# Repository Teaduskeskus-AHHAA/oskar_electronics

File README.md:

# Oskar III electronics

This repository contains the hardware and firmware sources required to build the electronic controllers for Science Centre AHHAA's Oskar III.

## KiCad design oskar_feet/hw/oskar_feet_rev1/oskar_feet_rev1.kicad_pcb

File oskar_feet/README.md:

# Oskar III electronics/Feet

This folder contains the contains the hardware and firmware sources required to build the electronic controller for Oskar III's feet. This controller handles the drivetrain and power control for the rest of the robot.

# Feature list

* IR Corner sensors
* Wheel engage-disengage control and detection
* Wheel drive
* Kneel drive
* BMS comms

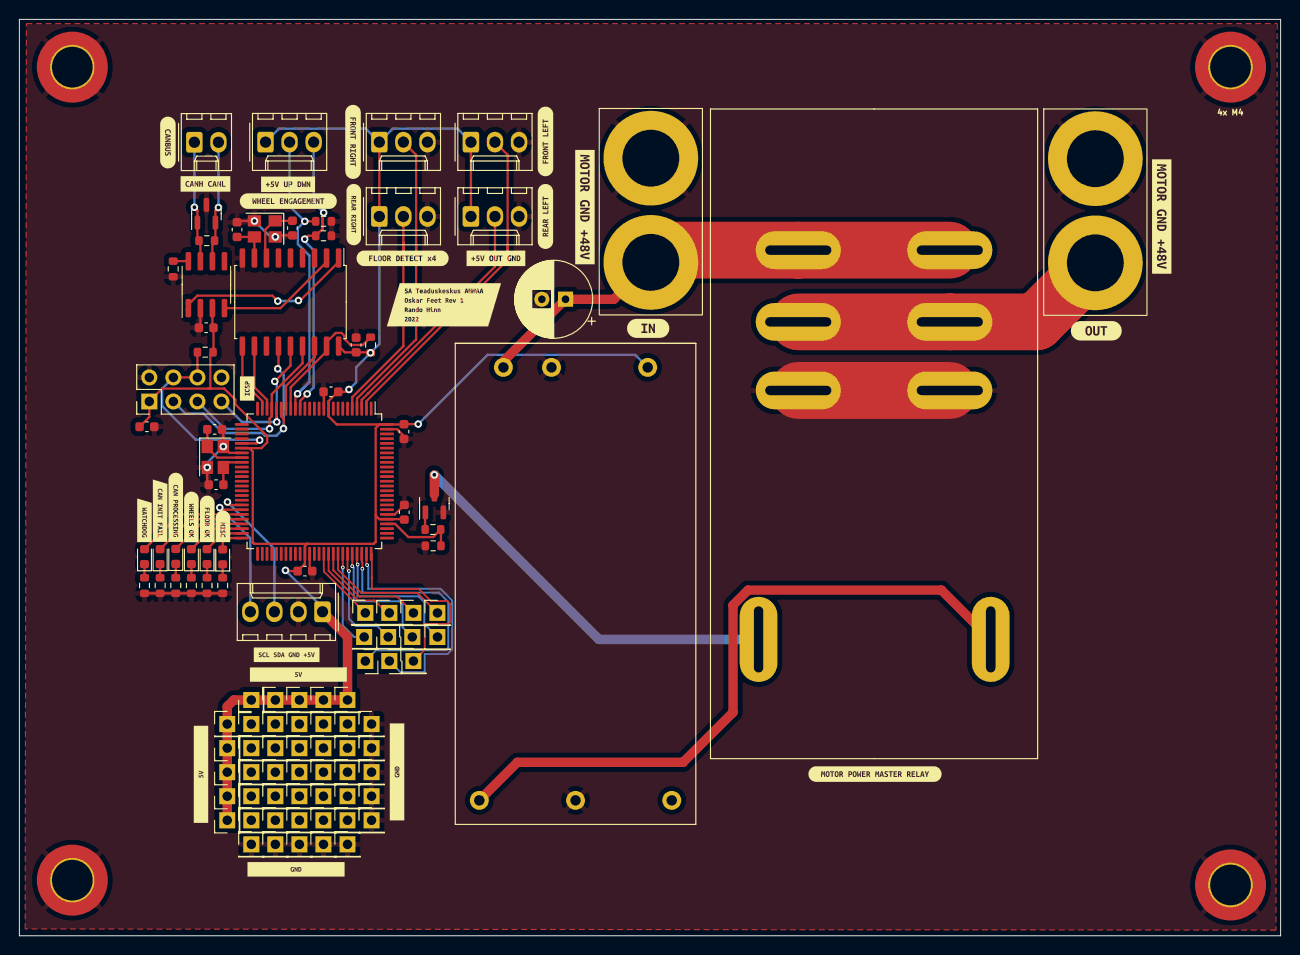
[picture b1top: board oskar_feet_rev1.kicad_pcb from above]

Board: 2 copper layers, 133.2 x 96.8 mm, 139 parts (0 on the bottom side), 56 nets.

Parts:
C1, C2, C5, C6, C7, C10, C11: 10u; C_0603_1608Metric
C3, C4, C8, C9: TBD; C_0603_1608Metric
C12: TBD; CP_Radial_D8.0mm_P2.50mm
D1: PESD2CAN; SOT-23
D2, D3, D4, D5, D6, D7: LED; LED_0603_1608Metric
H1, H2, H3, H4: MountingHole_Pad; MountingHole_4.3mm_M4_DIN965_Pad_TopBottom
J1: PROG; PinHeader_2x04_P2.54mm_Vertical
J2: Conn_01x02_Male; Molex_KK-254_AE-6410-02A_1x02_P2.54mm_Vertical
J3, J4, J5, J6, J9: Conn_01x03_Male; Molex_KK-254_AE-6410-03A_1x03_P2.54mm_Vertical
J7: Conn_01x02_Female; XT90
J8: Conn_01x02_Male; XT90
J10: Conn_01x04_Male; Molex_KK-254_AE-6410-04A_1x04_P2.54mm_Vertical
J11, J12, J13, J14, J15, J16, J17, J18, J19, J20, J21, J22, J23, J24, J25, J26, J27, J28, J29, J30, J31, J32, J33, J34, J35, J36, J37, J38, J39, J40, J41, J42, J43, J44, J45, J46, J47, J48, J49, J50, J51, J52, J53, J54, J55, J56, J58, J59, J60, J61, J62, J63, J64, J65, J66, J67: Conn_01x01_Male; PinHeader_1x01_P2.54mm_Vertical
K1: T92P11D22-12
Q1: BC817; SOT-23
R1, R2, R4, R6, R13, R14: 10k; R_0603_1608Metric
R3: 120; R_0603_1608Metric
R5: 330; R_0603_1608Metric
R7, R8, R9, R10, R11, R12: tbd; R_0603_1608Metric
U1: ATmega2560-16A; TQFP-100_14x14mm_P0.5mm
U2: MCP2515-xSO; SOIC-18W_7.5x11.6mm_P1.27mm
U3: MCP2551-I-SN; SOIC-8_3.9x4.9mm_P1.27mm
U4: MPRB4812LD-30W
Y1, Y3: Crystal_GND24; Crystal_SMD_Abracon_ABM8G-4Pin_3.2x2.5mm
kibuzzard-61FBB8B4: G***; kibuzzard-61FBB8B4
kibuzzard-61FBB827: G***; kibuzzard-61FBB827
kibuzzard-61FBB893: G***; kibuzzard-61FBB893
kibuzzard-61FBB948: G***; kibuzzard-61FBB948
kibuzzard-61FBBA02: G***; kibuzzard-61FBBA02
kibuzzard-61FBBA21: G***; kibuzzard-61FBBA21
kibuzzard-61FBBAE0: G***; kibuzzard-61FBBAE0
kibuzzard-61FC1DAC: G***; kibuzzard-61FC1DAC
kibuzzard-620D462F: G***; kibuzzard-620D462F
kibuzzard-620D4636: G***; kibuzzard-620D4636
kibuzzard-620D4649, kibuzzard-620D4649#2: G***; kibuzzard-620D4649
kibuzzard-620F6F5F: G***; kibuzzard-620F6F5F
kibuzzard-620F6F6C: G***; kibuzzard-620F6F6C
kibuzzard-622DE651: G***; kibuzzard-622DE651
kibuzzard-622E021D: G***; kibuzzard-622E021D
kibuzzard-622E0128: G***; kibuzzard-622E0128
kibuzzard-622E0245: G***; kibuzzard-622E0245
kibuzzard-622E0709: G***; kibuzzard-622E0709
kibuzzard-622E0714: G***; kibuzzard-622E0714
kibuzzard-623B0250: G***; kibuzzard-623B0250
kibuzzard-625E7F56, kibuzzard-625E7F56#2: G***; kibuzzard-625E7F56
kibuzzard-625E7F64, kibuzzard-625E7F64#2: G***; kibuzzard-625E7F64
kibuzzard-62568EE0: G***; kibuzzard-62568EE0
kibuzzard-62568F06: G***; kibuzzard-62568F06
kibuzzard-6256903B: G***; kibuzzard-6256903B

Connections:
+5V: C1.1, C2.1, C5.2, C6.1, C7.1, C10.1, C11.1, J1.1, J3.1, J4.1, J5.1, J6.1, J9.1, J10.1, J11.1, J12.1, J13.1, J14.1, J15.1, J16.1, J17.1, J18.1, J19.1, J20.1, R1.1, R4.1, U1.10 (VCC), U1.31 (VCC), U1.61 (VCC), U1.80 (VCC), U1.100 (AVCC), U2.18 (VDD), U3.3 (VDD), U4.1 (Ctrl)
+12V: K1.2, U4.4 (+Vo)
+48V: C12.1, J8.2, K1.3, K1.4, U4.3 (Vin)
/CANRESET: R4.2, U1.18 (PH6), U2.17 (~RESET)
/CAN_SS: U1.19 (PB0), U2.16 (~CS)
/CORNER_SENSOR_FL: J6.2, U1.2 (PE0)
/CORNER_SENSOR_FR: J5.2, U1.4 (PE2)
/CORNER_SENSOR_RL: J3.2, U1.3 (PE1)
/CORNER_SENSOR_RR: J4.2, U1.5 (PE3)
/LED1: D2.2 (A), U1.45 (PD2)
/LED2: D3.2 (A), U1.46 (PD3)
/LED3: D4.2 (A), U1.47 (PD4)
/LED4: D5.2 (A), U1.48 (PD5)
/LED5: D6.2 (A), U1.49 (PD6)
/LED6: D7.2 (A), U1.50 (PD7)
/MISO: J1.5, U1.22 (PB3), U2.15 (SO)
/MOSI: J1.7, U1.21 (PB2), U2.14 (SI)
/MOTOR_PWR_EN: R5.1, R6.2, U1.79 (PJ7)
/OSC1: C9.1, U2.8 (OSC1), Y1.3
/OSC2: C8.2, U2.7 (OSC2), Y1.1
/RESET: J1.4, J1.6, R1.2, U1.30 (~RESET)
/RX0BF: U1.23 (PB4), U2.11 (~RX0BF)
/RX1BF: U1.24 (PB5), U2.10 (~RX1BF)
/RXCAN: U2.2 (RXCAN), U3.4 (RXD)
/SCK: J1.3, U1.20 (PB1), U2.13 (SCK)
/SCL: J10.3, U1.43 (PD0)
/SDA: J10.4, U1.44 (PD1)
/TXCAN: U2.1 (TXCAN), U3.1 (TXD)
/WHEEL_ENGAGEMENT_LOWER: J9.3, R14.1, U1.16 (PH4)
/WHEEL_ENGAGEMENT_UPPER: J9.2, R13.1, U1.17 (PH5)
/XTAL1: C3.2, U1.34 (XTAL1), Y3.3
/XTAL2: C4.1, U1.33 (XTAL2), Y3.1
GND: C1.2, C2.2, C3.1, C4.2, C5.1, C6.2, C7.2, C8.1, C9.2, C10.2, C11.2, C12.2, D1.3 (A), H1.1, H2.1, H3.1, H4.1, J1.2, J3.3, J4.3, J5.3, J6.3, J7.1, J8.1, J10.2, J21.1, J22.1, J23.1, J24.1, J25.1, J26.1, J27.1, J28.1, J29.1, J30.1, K1.7, K1.8, Q1.2 (E), R2.2, R6.1, R7.1, R8.1, R9.1, R10.1, R11.1, R12.1, R13.2, R14.2, U1.11 (GND), U1.32 (GND), U1.62 (GND), U1.81 (GND), U1.99 (GND), U2.9 (VSS), U3.2 (VSS), U4.2 (GND), U4.5 (0V), Y1.2, Y1.4, Y3.2, Y3.4
unnamed: D1.1 (K), J2.1, R3.1, U3.7 (CANH)
unnamed: D1.2 (K), J2.2, R3.2, U3.6 (CANL)
unnamed: D2.1 (K), R7.2
unnamed: D3.1 (K), R8.2
unnamed: D4.1 (K), R9.2
unnamed: D5.1 (K), R10.2
unnamed: D6.1 (K), R11.2
unnamed: D7.1 (K), R12.2
unnamed: J7.2, K1.5, K1.6
unnamed: K1.1, Q1.3 (C)
unnamed: Q1.1 (B), R5.2
unnamed: R2.1, U3.8 (Rs)
unnamed: J58.1, U1.65 (PJ2)
unnamed: J59.1, U1.66 (PJ3)
unnamed: J60.1, U1.67 (PJ4)
unnamed: J61.1, U1.68 (PJ5)
unnamed: J62.1, U1.69 (PJ6)
unnamed: J63.1, U1.70 (PG2)
unnamed: J67.1, U1.71 (PA7)
unnamed: J66.1, U1.72 (PA6)
unnamed: J65.1, U1.73 (PA5)
unnamed: J64.1, U1.74 (PA4)
unnamed: J56.1, U1.75 (PA3)

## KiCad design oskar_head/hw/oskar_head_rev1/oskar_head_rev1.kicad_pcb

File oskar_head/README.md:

# Oskar III electronics/Head

This folder contains the contains the hardware and firmware sources required to build the electronic controller for Oskar III's head. This controller handles the eyes, mouth and eyebrows for the robot.

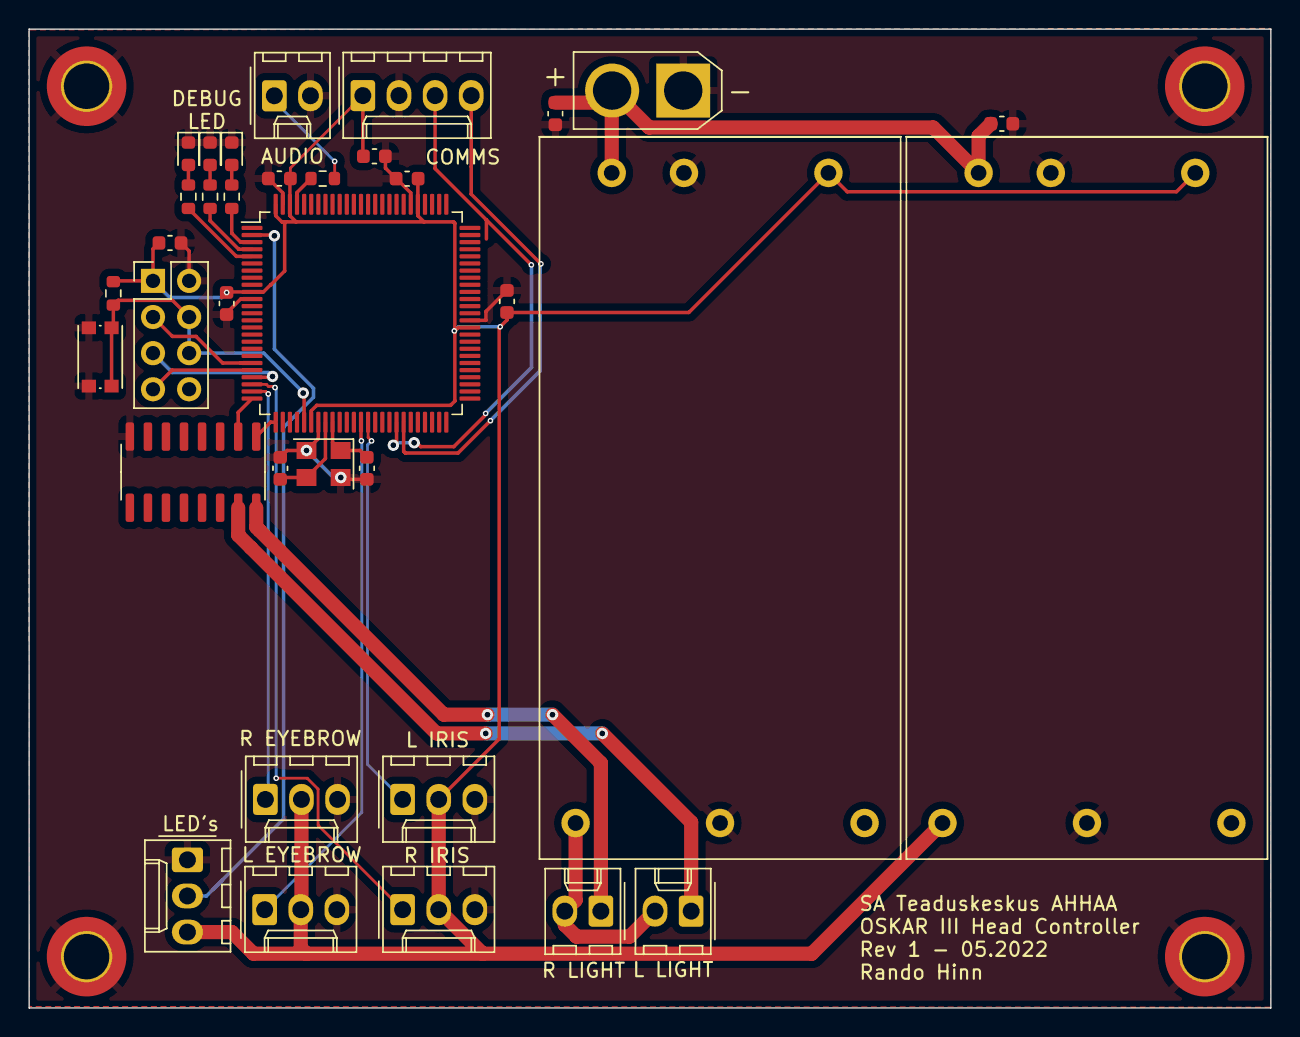
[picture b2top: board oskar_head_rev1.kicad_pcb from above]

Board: 2 copper layers, 87.3 x 68.8 mm, 39 parts (0 on the bottom side), 29 nets.

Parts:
C1, C2, C3, C4, C6, C9, C10, C11: 10u; C_0603_1608Metric
C7, C8: TBD; C_0603_1608Metric
D1, D2, D3: LED_Small; LED_0603_1608Metric
H1, H2, H3, H4: MountingHole_Pad; MountingHole_3.2mm_M3_DIN965_Pad_TopBottom
J1: Conn_02x04_Odd_Even; PinHeader_2x04_P2.54mm_Vertical
J2: Conn_01x02_Male; AMASS_XT30U-M_1x02_P5.0mm_Vertical
J3, J4, J7: Conn_01x02_Male; Molex_KK-254_AE-6410-02A_1x02_P2.54mm_Vertical
J5: Conn_01x03_Male; Molex_KK-254_AE-6410-03A_1x03_P2.54mm_Vertical
J6: Conn_01x04_Male; Molex_KK-254_AE-6410-04A_1x04_P2.54mm_Vertical
M1, M2, M3, M4: Motor_Servo; Molex_KK-254_AE-6410-03A_1x03_P2.54mm_Vertical
R1: 10k; R_0603_1608Metric
R2, R3, R4, R5: R_Small; R_0603_1608Metric
SW1: SW_Push; SW_Push_1P1T_NO_CK_KMR2
U1: ATmega2560-16A; TQFP-100_14x14mm_P0.5mm
U2: ULN2003A; SOP-16_3.9x9.9mm_P1.27mm
U3: MPRB4815LD-30W; MPRB4812LD-30W
U4: MPRB4805LD-30W; MPRB4812LD-30W
Y1: 16 MHz; Crystal_SMD_SeikoEpson_FA238V-4Pin_3.2x2.5mm

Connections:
+5V: C1.2, C2.2, C3.2, C4.2, C6.2, C10.2, J1.1, J5.3, J6.1, M1.2 (+), M2.2 (+), M3.2 (+), M4.2 (+), R1.1, U1.10 (VCC), U1.31 (VCC), U1.61 (VCC), U1.80 (VCC), U1.98 (AREF), U1.100 (AVCC), U3.1 (Ctrl), U4.1 (Ctrl), U4.4 (+Vo)
+15V: J3.2, J4.2, U3.4 (+Vo)
+48V: C9.2, C11.2, J2.2, U3.3 (Vin), U4.3 (Vin)
/A_IN: R2.2, U1.97 (PF0)
/L_BROW: M2.1 (PWM), U1.38 (PL3)
/L_IRIS: M1.1 (PWM), U1.39 (PL4)
/L_LIGHT: J3.1, U2.15 (O2)
/L_LIGHT_PWM: U1.25 (PB6), U2.2 (I2)
/MISO: J1.5, U1.22 (PB3)
/MOSI: J1.7, U1.21 (PB2)
/PX_LED: J5.2, U1.2 (PE0)
/RESET: J1.4, J1.6, R1.2, SW1.2, U1.30 (~RESET)
/R_BROW: M4.1 (PWM), U1.24 (PB5)
/R_IRIS: M3.1 (PWM), U1.23 (PB4)
/R_LIGHT: J4.1, U2.16 (O1)
/R_LIGHT_PWM: U1.26 (PB7), U2.1 (I1)
/SCK: J1.3, U1.20 (PB1)
/SCL: J6.3, U1.43 (PD0)
/SDA: J6.4, U1.44 (PD1)
/XTAL1: C7.2, U1.34 (XTAL1), Y1.1
/XTAL2: C8.2, U1.33 (XTAL2), Y1.3
GND: C1.1, C2.1, C3.1, C4.1, C6.1, C7.1, C8.1, C9.1, C10.1, C11.1, D1.1 (K), D2.1 (K), D3.1 (K), H1.1, H2.1, H3.1, H4.1, J1.2, J2.1, J5.1, J6.2, J7.2, M1.3 (-), M2.3 (-), M3.3 (-), M4.3 (-), SW1.1, U1.11 (GND), U1.32 (GND), U1.62 (GND), U1.81 (GND), U1.99 (GND), U2.8 (GND), U3.2 (GND), U3.5 (0V), U4.2 (GND), U4.5 (0V), Y1.2, Y1.4
unnamed: D1.2 (A), R3.2
unnamed: D2.2 (A), R4.2
unnamed: D3.2 (A), R5.2
unnamed: J7.1, R2.1
unnamed: R3.1, U1.3 (PE1)
unnamed: R4.1, U1.4 (PE2)
unnamed: R5.1, U1.5 (PE3)

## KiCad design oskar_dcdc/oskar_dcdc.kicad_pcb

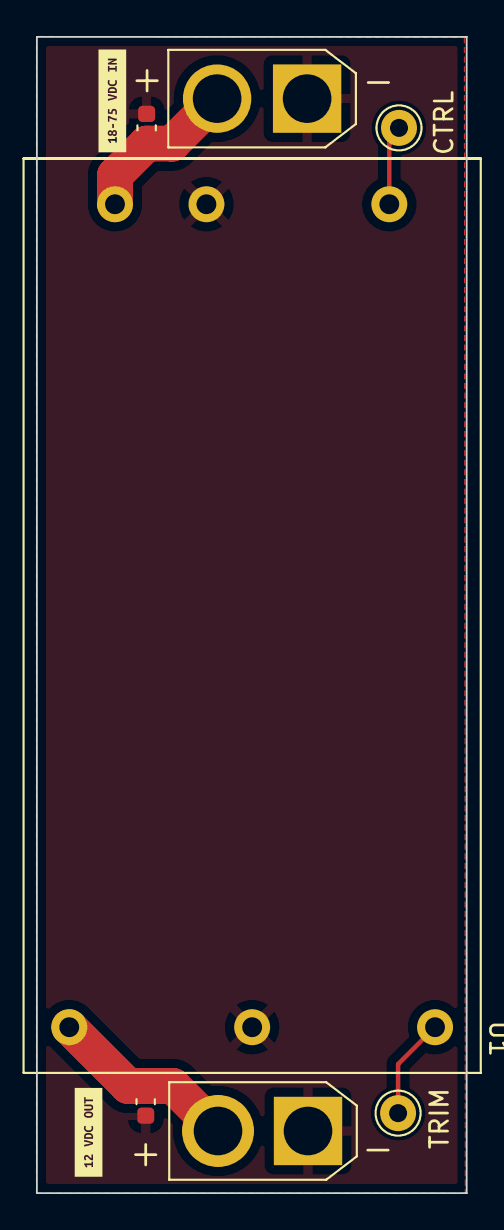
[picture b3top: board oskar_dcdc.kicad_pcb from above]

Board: 2 copper layers, 23.9 x 64.2 mm, 9 parts (0 on the bottom side), 5 nets.

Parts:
C1, C2: C_Small; C_0603_1608Metric
J1: Conn_01x02_Female; AMASS_XT30U-M_1x02_P5.0mm_Vertical
J2, J3: Conn_01x01_Female; Pin_D1.0mm_L10.0mm
J4: Conn_01x02_Female; AMASS_XT30U-F_1x02_P5.0mm_Vertical
U1: MPRB4812LD-30W
kibuzzard-625E65AB: G***; kibuzzard-625E65AB
kibuzzard-625E659B: G***; kibuzzard-625E659B

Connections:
GND: C1.2, C2.2, J1.1, J4.1, U1.2 (GND), U1.5 (0V)
unnamed: C1.1, J1.2, U1.3 (Vin)
unnamed: C2.1, J4.2, U1.4 (+Vo)
unnamed: J2.1, U1.1 (Ctrl)
unnamed: J3.1, U1.6 (Trim/-Vo)

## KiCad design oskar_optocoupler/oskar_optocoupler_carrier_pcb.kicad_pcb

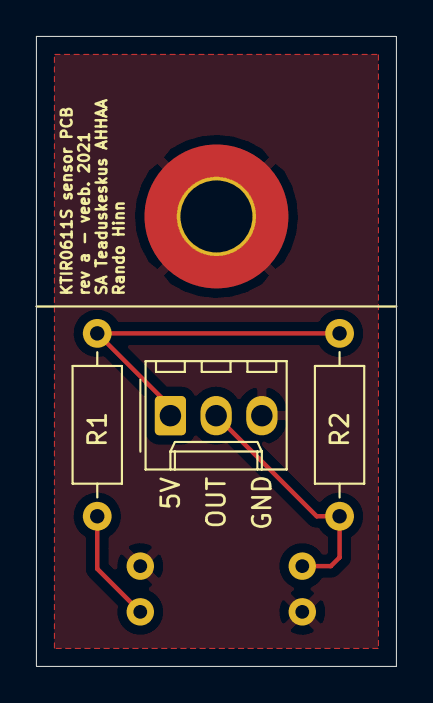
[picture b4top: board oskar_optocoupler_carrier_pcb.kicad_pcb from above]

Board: 2 copper layers, 20.0 x 35.0 mm, 5 parts (1 on the bottom side), 4 nets.

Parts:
J1: Conn_01x03_Male; Molex_KK-254_AE-6410-03A_1x03_P2.54mm_Vertical
J2: Conn_01x01_Female; MountingHole_4mm_Pad_TopBottom
R1: 560; R_Axial_DIN0207_L6.3mm_D2.5mm_P10.16mm_Horizontal
R2: 1.5k; R_Axial_DIN0207_L6.3mm_D2.5mm_P10.16mm_Horizontal
U1: KTIR0611S

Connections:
+5V: J1.1, R1.2, R2.2
/Output: J1.2, R2.1, U1.3
GND: J1.3, J2.1, U1.2, U1.4
unnamed: R1.1, U1.1

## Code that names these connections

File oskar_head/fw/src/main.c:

#include <avr/io.h>
#define F_CPU 16000000UL
#include <util/delay.h>
#include <avr/interrupt.h>
#include "include/ws2812_config.h"

#include "include/light_ws2812.h"
#include <stdlib.h>
#define NS_PER_SEC (1000000000L) // Note that this has to be SIGNED since we want to be able to check for negative values of derivatives
#define CYCLES_PER_SEC (F_CPU)
#define NS_PER_CYCLE (NS_PER_SEC / CYCLES_PER_SEC)
#define NS_TO_CYCLES(light_n) ((n) / NS_PER_CYCLE)
#define SBI(port, bit) asm volatile("sbi %0,%1" ::"I"(_SFR_IO_ADDR(port)), "I"(bit))
#define cbi(port, bit) port = ~(1 << bit)
uint16_t count = 0;

struct cRGB led[2];

uint16_t read_adc(uint8_t ch)
{
  ch &= 0b00000111;            // Constrain 0-7
  ADMUX = (ADMUX & 0xF8) | ch; // Tyhistame MUX-is praeguse valiku, ja OR-ime enda asja sisse.
  ADCSRA |= (1 << ADSC);
  while (ADCSRA & (1 << ADSC))
  {
  }

  return (ADC);
}

void doColor(uint32_t col)
{
  cli();
  uint8_t i;
  for (i = 24; i;)
  {
    if (col & 0x800000)
    {
      PORTE |= (1 << PE0);
      _delay_us(0.7);
      i--;
      col <<= 1;
      PORTE &= ~(1 << PE0);
      _delay_us(0.6);
    }
    else
    {
      PORTE |= (1 << PE0);
      _delay_us(0.35);
      i--;
      cbi(PORTE, 0);
      col <<= 1;
      _delay_us(0.8);
    }
  }
  sei();
}

void blink()
{
  PORTE &= ~(1 << PE1);
  PORTB &= ~((1 << PB6) | (1 << PB7));
  _delay_ms(100);
  PORTE |= (1 << PE1);
  PORTB |= (1 << PB6) | (1 << PB7);
}

int main()
{

  ADMUX = (1 << REFS0);
  ADCSRA = (1 << ADPS1) | (1 << ADPS2) | (1 << ADEN); // Prescaler 64

  DDRE |= (1 << DDE0) | (1 << DDE1) | (1 << DDE2) | (1 << DDE3);

  DDRB |= (1 << DDB6) | (1 << DDB7);

  PORTB |= (1 << PB6) | (1 << PB7);

  PORTE |= (1 << PE1);

  led[0].r = 255;
  led[0].g = 255;
  led[0].b = 255; // Write red to array

  led[1].r = 255;
  led[1].g = 255;
  led[1].b = 255; // Write red to array

  blink();
  _delay_ms(1000);
  blink();

  while (1)
  {
    /* doColor(0xFF00FF);
     _delay_ms(1);
     ws2812_setleds(led, 2);*/

    uint16_t randbase = read_adc(13);
    if (randbase % 3)
    {
      count++;
    }
    if (count >= 50000)
    {
      blink();
      count = 0;
    }
  }
  return 0;
}

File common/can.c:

#include "include/can.h"
#include "include/spi.h"

void CAN_set_mode(uint8_t mode)
{
  SPI_unset_cs();
  SPI_write(BIT_MODIFY);
  SPI_write(CANCTRL);
  SPI_write(REQOP_MASK);
  SPI_write((mode << REQOP_OFFSET));
  SPI_set_cs();
}

uint8_t CAN_init(uint8_t freq_meg, long baudrate)
{
  CAN_set_mode(REQOP_CONFIG);
  while (!(CAN_read_register(CANSTAT) & 0x80))
  {
  };

  /* https://www.kvaser.com/support/calculators/bit-timing-calculator/ (16MHz, 1Mbps, MCP2510)*/
  uint8_t cnf1 = 0x00;
  uint8_t cnf2 = 0x91;
  uint8_t cnf3 = 0x01;

  CAN_set_register(CNF1, cnf1);
  CAN_set_register(CNF2, cnf2);
  CAN_set_register(CNF3, cnf3);

  CAN_set_register(RXB0CTRL, 0x64); // FIlters off, rollover enable
  CAN_set_register(RXB1CTRL, 0x60); // FIlters off

  CAN_set_register(BFPCTRL, 0b00001111);

  CAN_set_register(TXB0CTRL, 0);
  CAN_set_register(TXB1CTRL, 0);
  CAN_set_register(TXB2CTRL, 0);
}

uint8_t CAN_read_register(uint8_t reg)
{
  SPI_unset_cs();
  SPI_write(READ);
  SPI_write(reg);
  SPI_write(0x00);
  SPI_set_cs();
  return SPDR;
}

void CAN_set_register(uint8_t reg, uint8_t value)
{
  SPI_unset_cs();
  SPI_write(WRITE);
  SPI_write(reg);
  SPI_write(value);
  SPI_set_cs();
}

uint8_t CAN_verify_register(uint8_t reg, uint8_t expected)
{
  uint8_t reading = CAN_read_register(reg);
  return (reading == expected);
}

uint8_t CAN_init_regcheck()
{
  /* https://www.kvaser.com/support/calculators/bit-timing-calculator/ (16MHz, 1Mbps, MCP2510)*/
  uint8_t c1 = 0x00;
  uint8_t c2 = 0x91;
  uint8_t c3 = 0x01;
  return CAN_verify_register(CNF1, c1) && CAN_verify_register(CNF2, c2) && CAN_verify_register(CNF3, c3);
}

void CAN_load_message(uint8_t buffer, CAN_frame_t *frame)
{
  SPI_unset_cs();
  SPI_write(LOAD_TX_BUFFER | buffer);
  SPI_write((frame->SID >> 3));
  SPI_write((frame->SID << 5));
  SPI_write(0);
  SPI_write(0);

  uint8_t length = frame->header.len & 0x0F;
  if (frame->header.rtr)
  {
    SPI_write((1 << RTR) | length);
  }
  else
  {
    SPI_write(length);
    uint8_t i;
    for (i = 0; i < length; i++)
    {
      SPI_write(frame->data[i]);
    }
  }
  SPI_set_cs();
}
void CAN_request_to_send(uint8_t buffer)
{
  uint8_t address = (buffer == 0) ? 1 : buffer;
  SPI_unset_cs();
  SPI_write(RTS | address);
  SPI_set_cs();
}

void CAN_read(uint8_t buffer, CAN_frame_t *frame)
{
  uint8_t metadata[5];
  if (buffer == 0)
  {
    CAN_read_registers(RXB0SIDH, metadata, 5);
    CAN_read_registers(RXB0D0, frame->data, 8);
    SPI_unset_cs();
    SPI_write(BIT_MODIFY);
    SPI_write(CANINTF);
    SPI_write(RX0IF);
    SPI_write(0);
    SPI_set_cs();
  }
  else if (buffer == 1)
  {
    CAN_read_registers(RXB1SIDH, metadata, 5);
    CAN_read_registers(RXB1D0, frame->data, 8);
    SPI_unset_cs();
    SPI_write(BIT_MODIFY);
    SPI_write(CANINTF);
    SPI_write(RX1IF);
    SPI_write(0);
    SPI_set_cs();
  }

  frame->SID = (metadata[0] << 3) | (metadata[1] >> 5);
  frame->header.len = metadata[4];
}

void CAN_read_registers(uint8_t start, uint8_t target[], uint8_t len)
{
  SPI_unset_cs();
  SPI_write(READ);
  SPI_write(start);
  for (int i = 0; i < len; i++)
  {
    SPI_write(0x00);
    target[i] = SPDR;
  }
  SPI_set_cs();
}

CAN_error CAN_send(CAN_frame_t *frame)
{
  uint8_t abort, lost, txerr;
  uint8_t txbuffer_full[3];
  txbuffer_full[0] = CAN_check_bit(TXB0CTRL, 0x08);
  txbuffer_full[1] = CAN_check_bit(TXB1CTRL, 0x08);
  txbuffer_full[2] = CAN_check_bit(TXB2CTRL, 0x08);

  int selected_buffer = -1;

  for (int i = 0; i < 3; i++)
  {
    if (!txbuffer_full[i])
    {
      selected_buffer = i;
      break;
    }
  }
  if (selected_buffer == -1)
  {

    PORTD |= (1 << PD2) | (1 << PD7);

    return CAN_ERROR_ALLTXBUSY;
  }

  switch (selected_buffer)
  {
  case 0:
    CAN_load_message(TXB0ADDR, frame);
    CAN_request_to_send(TXB0ADDR);
    abort = CAN_check_bit(TXB0ADDR, ABTF);
    lost = CAN_check_bit(TXB0ADDR, MLOA);
    txerr = CAN_check_bit(TXB0ADDR, TXERR);
    break;
  case 1:
    CAN_load_message(TXB1ADDR, frame);
    CAN_request_to_send(TXB1ADDR);
    abort = CAN_check_bit(TXB1ADDR, ABTF);
    lost = CAN_check_bit(TXB1ADDR, MLOA);
    txerr = CAN_check_bit(TXB1ADDR, TXERR);
    break;
  case 2:
    CAN_load_message(TXB2ADDR, frame);
    CAN_request_to_send(TXB2ADDR);
    abort = CAN_check_bit(TXB2ADDR, ABTF);
    lost = CAN_check_bit(TXB2ADDR, MLOA);
    txerr = CAN_check_bit(TXB2ADDR, TXERR);
    break;
  default:
    PORTD |= (1 << PD2);
    return CAN_ERROR_UNKNOWN_FLOW;
  }

  if (abort)
  {
    PORTD |= (1 << PD5);
    return CAN_ERROR_ABORT;
  }
  if (lost)
  {
    PORTD |= (1 << PD6);
    return CAN_ERROR_LOSTARBITATION;
  }
  if (txerr)
  {
    PORTD |= (1 << PD7);
    return CAN_ERROR_TXERR;
  }

  return CAN_ERROR_NONE;
}

uint8_t CAN_check_bit(uint8_t reg, uint8_t bitmask)
{
  return CAN_read_register(reg) & bitmask;
}

uint8_t CAN_get_TEC()
{
  return CAN_read_register(0x1C);
}

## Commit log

2021-12-28 Add readme's for each folder
2021-12-28 Move optocoupler carrier PCB to this repo.
2021-12-28 Unlink optocoupler from it's previous git repo.
2022-01-20 Beginnings of feet controller electronics and moving of some firmware components.
2022-02-03 Feet controller. Start some bits of layouting. Add Motor power relay
2022-07-11 KICAD
2022-07-11 WIP Firmware & Bugs
